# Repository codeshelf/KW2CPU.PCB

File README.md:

KW2CPU.PCB
==========

KW2 radio / CPU PCB design files (with production files). "Brain"

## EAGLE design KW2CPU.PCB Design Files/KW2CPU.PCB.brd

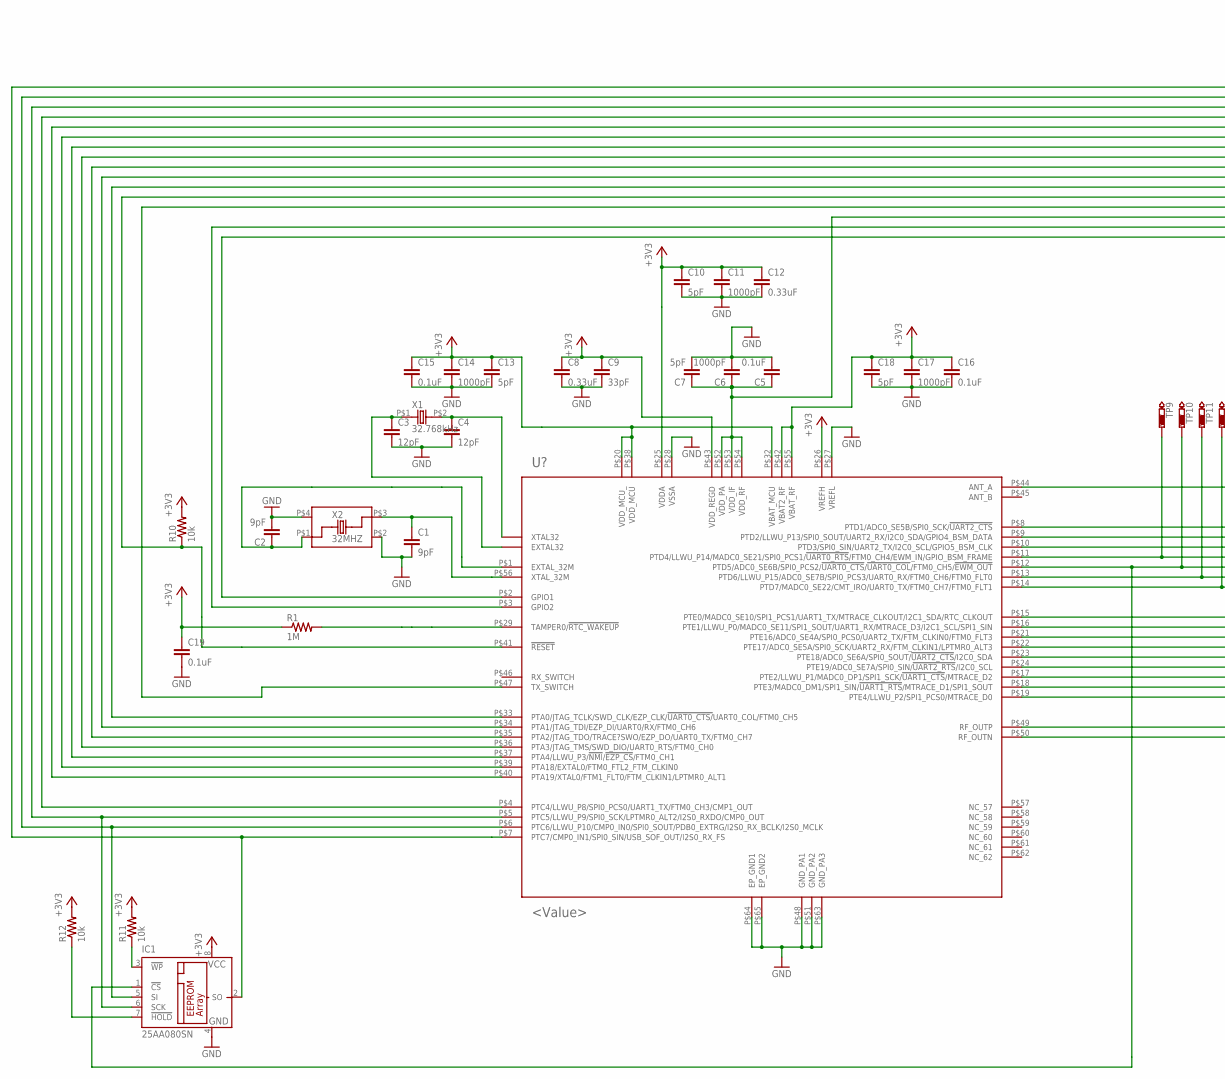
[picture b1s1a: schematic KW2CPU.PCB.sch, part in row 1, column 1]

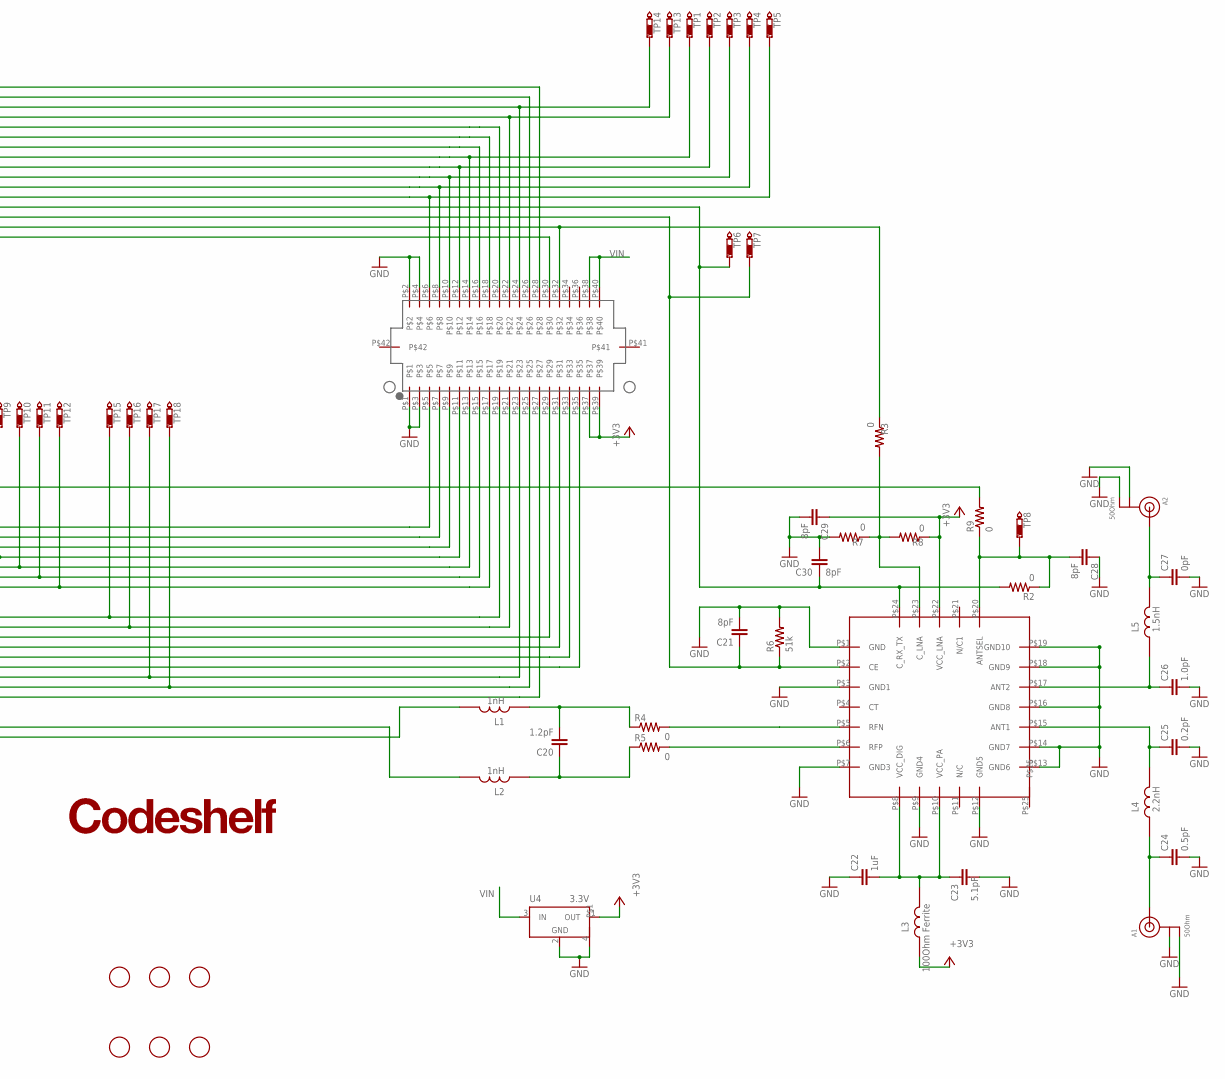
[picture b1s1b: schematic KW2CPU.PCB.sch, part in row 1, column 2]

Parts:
A1, A2: 50Ohm; U.FL
C1, C2: 9pF; C0402
C3, C4: 12pF; C0402
C5, C15, C16, C19: 0.1uF; C0402
C6, C11, C14, C17: 1000pF; C0402
C7, C10, C13, C18: 5pF; C0402
C8, C12: 0.33uF; C0402
C9: 33pF; C0402
C20: 1.2pF; RF-L0201
C21, C28, C29, C30: 8pF; RFMD0402
C22: 1uF; RF-L0201
C23: 5.1pF; RF-L0201
C24: 0.5pF; RFMD0402
C25: 0.2pF; RFMD0402
C26: 1.0pF; RFMD0402
C27: 0pF; RFMD0402
IC1: 25AA080SN; SO-08; MPN 25AA640A
J1: DF12_M
L1, L2: 1nH; RF-L0201
L3: 100Ohm Ferrite; RFMD0402
L4: 2.2nH; RFMD0402
L5: 1.5nH; RFMD0402
R1: 1M; RF-R0402
R2, R3, R7, R8, R9: 0; RFMD0402
R4, R5: 0; RF-L0201
R6: 51k; RFMD0402
R10, R11, R12: 10k; RF-R0402
TP1, TP2, TP3, TP4, TP5, TP6, TP7, TP8, TP9, TP10, TP11, TP12, TP13, TP14, TP15, TP16, TP17, TP18: PTR1TP15R; TP15R
U1: MKW21D; LGA63
U3: RF6555
U4: 3.3V; SOT223
U$1: CODESHELF-LOGOSMALL; CODESHELF-LOGO-SMALL
U$2, U$3, U$4, U$5, U$6, U$7: FIDUCIAL; FIDUCIAL_1MM
X1: 32.768kHz; 32KHZSMD
X2: 32MHZ; 32MHZSMD

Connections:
!HOLD: IC1.7 (!HOLD), R12.1
!RESET: J1.P$6, R10.1, TP5.TP, U1.P$41 (!RESET)
!WP: IC1.3 (!WP), R11.1
+3V3: C8.1, C9.1, C10.1, C11.1, C12.1, C13.1, C14.1, C15.1, C16.1, C17.1, C18.1, C19.1, C29.P$1 (1), IC1.8 (VCC), J1.P$37, J1.P$39, L3.P$2 (2), R1.1, R8.P$1 (1), R10.2, R11.2, R12.2, U1.P$20 (VDD_MCU_), U1.P$25 (VDDA), U1.P$26 (VREFH), U1.P$32 (VBAT_MCU), U1.P$38 (VDD_MCU), U1.P$42 (VBAT2_RF), U1.P$43 (VDD_REGD), U1.P$55 (VBAT_RF), U3.P$22 (VCC_LNA), U4.1 (OUT)
ANT1: C25.P$1 (1), L4.P$1 (1), U3.P$15 (ANT1)
ANT2: C26.P$1 (1), L5.P$2 (2), U3.P$17 (ANT2)
ANTSEL: C28.P$2 (2), R2.P$1 (1), R9.P$1 (1), TP8.TP, U3.P$20 (ANTSEL)
ANT_A: R9.P$2 (2), U1.P$44 (ANT_A)
C_LNA: R3.P$2 (2), R7.P$1 (1), R8.P$2 (2), U3.P$23 (C_LNA)
EXTAL32: C3.1, U1.P$31 (EXTAL32), X1.P$1 (1)
EXTAL_32M: C2.1, U1.P$1 (EXTAL_32M), X2.P$1
GND: A1.1 (GND), A1.2 (GND), A2.1 (GND), A2.2 (GND), C1.2, C2.2, C3.2, C4.2, C5.2, C6.2, C7.2, C8.2, C9.2, C10.2, C11.2, C12.2, C13.2, C14.2, C15.2, C16.2, C17.2, C18.2, C19.2, C21.P$2 (2), C22.P$1 (1), C23.P$2 (2), C24.P$2 (2), C25.P$2 (2), C26.P$2 (2), C27.P$2 (2), C28.P$1 (1), C29.P$2 (2), C30.P$1 (1), IC1.4 (GND), J1.P$1, J1.P$2, J1.P$3, J1.P$4, R6.P$2 (2), R7.P$2 (2), U1.P$27 (VREFL), U1.P$28 (VSSA), U1.P$48 (GND_PA1), U1.P$51 (GND_PA2), U1.P$63 (GND_PA3), U1.P$64 (EP_GND1), U1.P$65 (EP_GND2), U3.P$1 (GND), U3.P$3 (GND1), U3.P$7 (GND3), U3.P$9 (GND4), U3.P$12 (GND5), U3.P$13 (GND6), U3.P$14 (GND7), U3.P$16 (GND8), U3.P$18 (GND9), U3.P$19 (GND10), U4.2 (GND), U4.4, X2.P$2, X2.P$4
GPIO1: J1.P$30, U1.P$2 (GPIO1)
GPIO2: J1.P$32, R3.P$1 (1), U1.P$3 (GPIO2)
PTA0/JTAG_TCLK/SWD_CLK/EZP_CLK/!UART0_CTS/!UART0_COL/FTM0_CH5: J1.P$8, TP4.TP, U1.P$33 (PTA0/JTAG_TCLK/SWD_CLK/EZP_CLK/!UART0_C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)
PTA1/JTAG_TDI/EZP_DI/UART0/RX/FTM0_CH6: J1.P$10, TP3.TP, U1.P$34 (PTA1/JTAG_TDI/EZP_DI/UART0/RX/FTM0_CH6)
PTA2/JTAG_TDO/TRACE?SWO/EZP_DO/UART0_TX/FTM0_CH7: J1.P$12, TP2.TP, U1.P$35 (PTA2/JTAG_TDO/TRACE?SWO/EZP_DO/UART0_TX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)
PTA3/JTAG_TMS/SWD_DIO/UART0_RTS/FTM0_CH0: J1.P$14, TP1.TP, U1.P$36 (PTA3/JTAG_TMS/SWD_DIO/UART0_RTS/FTM0_CH0)
PTA4/LLWU_P3/!NMI!/!EZP_CS!/FTM0_CH1: J1.P$16, U1.P$37 (PTA4/LLWU_P3/!NMI!/!EZP_CS!/FTM0_CH1)
PTA18/EXTAL0/FTM0_FTL2_FTM_CLKIN0: J1.P$18, U1.P$39 (PTA18/EXTAL0/FTM0_FTL2_FTM_CLKIN0)
PTA19/XTAL0/FTM1_FLT0/FTM_CLKIN1/LPTMR0_ALT1: J1.P$20, U1.P$40 (PTA19/XTAL0/FTM1_FLT0/FTM_CLKIN1/LPTMR0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)
PTC4/LLWU_P8/SPI0_PCS0/UART1_TX/FTM0_CH3/CMP1_OUT: J1.P$22, TP13.TP, U1.P$4 (PTC4/LLWU_P8/SPI0_PCS0/UART1_TX/FTM0_CH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)
PTC5/LLWU_P9/SPI0_SCK/LPTMR0_ALT2/I2S0_RXDO/CMP0_OUT: IC1.6 (SCK), J1.P$24, TP14.TP, U1.P$5 (PTC5/LLWU_P9/SPI0_SCK/LPTMR0_ALT2/I2S0_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)
PTC6/LLWU_P10/CMP0_IN0/SPI0_SOUT/PDB0_EXTRG/I2S0_RX_BCLK/I2S0_MCLK: IC1.5 (SI), J1.P$26, U1.P$6 (PTC6/LLWU_P10/CMP0_IN0/SPI0_SOUT/PDB0_E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)
PTC7/CMP0_IN1/SPI0_SIN/USB_SOF_OUT/I2S0_RX_FS: IC1.2 (SO), J1.P$28, U1.P$7 (PTC7/CMP0_IN1/SPI0_SIN/USB_SOF_OUT/I2S0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)
PTD1/ADC0_SE5B/SPI0_SCK/!UART2_CTS: J1.P$5, U1.P$8 (PTD1/ADC0_SE5B/SPI0_SCK/!UART2_CTS)
PTD2/LLWU_P13/SPI0_SOUT/UART2_RX/I2C0_SDA/GPIO4_BSM_DATA: J1.P$7, U1.P$9 (PTD2/LLWU_P13/SPI0_SOUT/UART2_RX/I2C0_S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)
PTD3/SPI0_SIN/UART2_TX/I2C0_SCL/GPIO5_BSM_CLK: J1.P$9, U1.P$10 (PTD3/SPI0_SIN/UART2_TX/I2C0_SCL/GPIO5_B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)
PTD4/LLWU_P14/MADC0_SE21/SPI0_PCS1/!UART0_RTS!/FTM0_CH4/EWM_IN/GPIO_BSM_FRAME: J1.P$11, TP9.TP, U1.P$11 (PTD4/LLWU_P14/MADC0_SE21/SPI0_PCS1/!UAR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)
PTD5/ADC0_SE6B/SPI0_PCS2/!UART0_CTS!/!UART0_COL!/FTM0_CH5/!EWM_OUT: IC1.1 (!CS), J1.P$13, TP10.TP, U1.P$12 (PTD5/ADC0_SE6B/SPI0_PCS2/!UART0_CTS!/!U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)
PTD6/LLWU_P15/ADC0_SE7B/SPI0_PCS3/UART0_RX/FTM0_CH6/FTM0_FLT0: J1.P$15, TP11.TP, U1.P$13 (PTD6/LLWU_P15/ADC0_SE7B/SPI0_PCS3/UART0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)
PTD7/MADC0_SE22/CMT_IRO/UART0_TX/FTM0_CH7/FTM0_FLT1: J1.P$17, TP12.TP, U1.P$14 (PTD7/MADC0_SE22/CMT_IRO/UART0_TX/FTM0_C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)
PTE0/MADC0_SE10/SPI1_PCS1/UART1_TX/MTRACE_CLKOUT/I2C1_SDA/RTC_CLKOUT: J1.P$19, TP15.TP, U1.P$15 (PTE0/MADC0_SE10/SPI1_PCS1/UART1_TX/MTRA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)
PTE1/LLWU_P0/MADC0_SE11/SPI1_SOUT/UART1_RX/MTRACE_D3/I2C1_SCL/SPI1_SIN: J1.P$21, TP16.TP, U1.P$16 (PTE1/LLWU_P0/MADC0_SE11/SPI1_SOUT/UART1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)
PTE2/LLWU_P1/MADC0_DP1/SPI1_SCK/!UART1_CTS!/MTRACE_D2: J1.P$23, TP17.TP, U1.P$17 (PTE2/LLWU_P1/MADC0_DP1/SPI1_SCK/!UART1_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)
PTE3/MADC0_DM1/SPI1_SIN/!UART1_RTS!/MTRACE_D1/SPI1_SOUT: J1.P$25, TP18.TP, U1.P$18 (PTE3/MADC0_DM1/SPI1_SIN/!UART1_RTS!/MTR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)
PTE4/LLWU_P2/SPI1_PCS0/MTRACE_D0: J1.P$27, U1.P$19 (PTE4/LLWU_P2/SPI1_PCS0/MTRACE_D0)
PTE16/ADC0_SE4A/SPI0_PCS0/UART2_TX/FTM_CLKIN0/FTM0_FLT3: J1.P$29, U1.P$21 (PTE16/ADC0_SE4A/SPI0_PCS0/UART2_TX/FTM_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)
PTE17/ADC0_SE5A/SPI0_SCK/UART2_RX/FTM_CLKIN1/LPTMR0_ALT3: J1.P$31, U1.P$22 (PTE17/ADC0_SE5A/SPI0_SCK/UART2_RX/FTM_C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)
PTE18/ADC0_SE6A/SPI0_SOUT/!UART2_CTS!/I2C0_SDA: J1.P$33, U1.P$23 (PTE18/ADC0_SE6A/SPI0_SOUT/!UART2_CTS!/I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)
PTE19/ADC0_SE7A/SPI0_SIN/!UART2_RTS!/I2C0_SCL: J1.P$35, U1.P$24 (PTE19/ADC0_SE7A/SPI0_SIN/!UART2_RTS!/I2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)
RADIO_AREG: C5.1, C6.1, C7.1, C21.P$1 (1), R6.P$1 (1), TP7.TP, U1.P$52 (VDD_PA), U1.P$53 (VDD_IF), U1.P$54 (VDD_RF), U3.P$2 (CE)
RFN: R4.P$2 (2), U3.P$5 (RFN)
RFN_MATCH: C20.P$2 (2), L1.P$2 (2), R4.P$1 (1)
RFP: R5.P$2 (2), U3.P$6 (RFP)
RFP_MATCH: C20.P$1 (1), L2.P$2 (2), R5.P$1 (1)
RF_OUTN: L1.P$1 (1), U1.P$50 (RF_OUTN)
RF_OUTP: L2.P$1 (1), U1.P$49 (RF_OUTP)
TAMPER/!RTC_WAKEUP: R1.2, U1.P$29 (TAMPER0/!RTC_WAKEUP)
TX_SWITCH: C30.P$2 (2), R2.P$2 (2), TP6.TP, U1.P$47 (TX_SWITCH), U3.P$24 (C_RX_TX)
U.FL.ANT1: A1.3 (SIGNAL), C24.P$1 (1), L4.P$2 (2)
U.FL.ANT2: A2.3 (SIGNAL), C27.P$1 (1), L5.P$1 (1)
VCC_DIG_PA: C22.P$2 (2), C23.P$1 (1), L3.P$1 (1), U3.P$8 (VCC_DIG), U3.P$10 (VCC_PA)
VIN: J1.P$38, J1.P$40, U4.3 (IN)
XTAL32: C4.1, U1.P$30 (XTAL32), X1.P$2 (2)
XTAL_32M: C1.1, U1.P$56 (XTAL_32M), X2.P$3

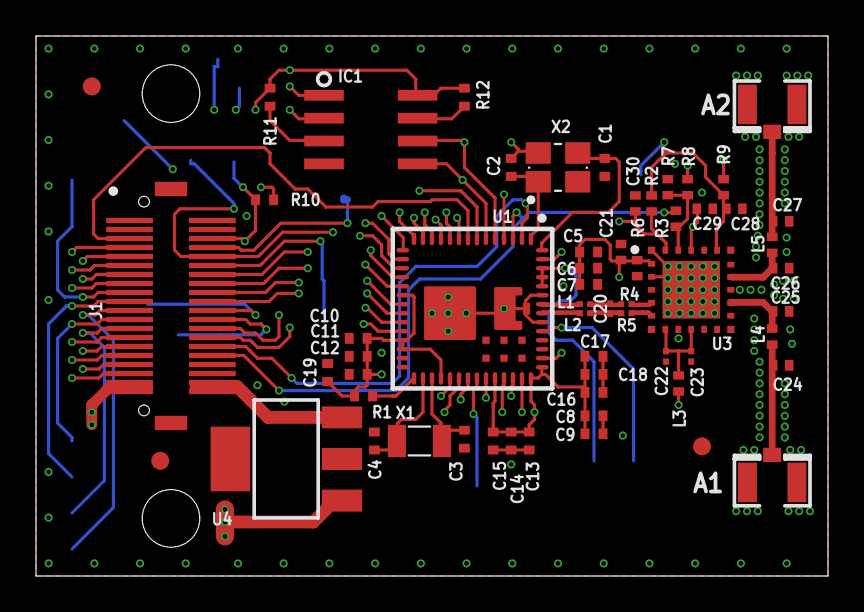
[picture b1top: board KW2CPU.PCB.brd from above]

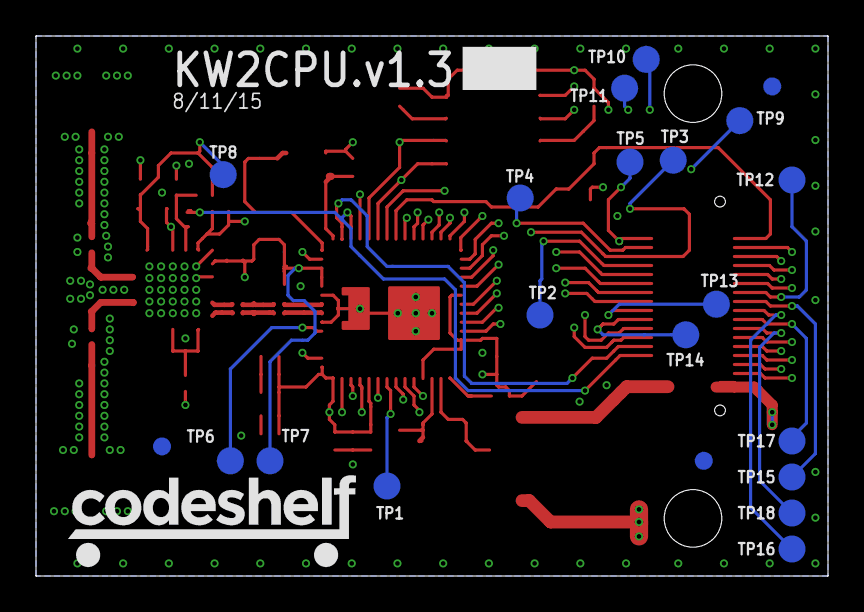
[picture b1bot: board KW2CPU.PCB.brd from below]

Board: 4 copper layers, 44.0 x 30.0 mm, 81 parts (22 on the bottom side), 56 nets.

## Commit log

2014-10-12 Imported KW2CPU design files
    Imported from Archive repo and deleted that one
2014-10-13 Working on layout
    ...4 layers is kind of annoying.
2014-10-13 Still routing
    :(
2014-10-18 Added JTAG
    Topside connector. Still needs routing
2014-10-21 JTAG, RF Conn trace
    Added JTAG connector, adjusted arcs on RF connector trace and added GND
    vias
2014-10-22 Random things
    Mostly playing with copper settings. No design changes
2014-10-31 Rotated board
2014-11-05 Schematic fix
    Almost done fixing schematic
2014-11-07 Added hacky JTAG board
    Terrible angles, but fininshed. Can be made in house (0.2mm)
2014-11-12 Labeled all nets
    Named nets and simplified JTAG adapter board.
2014-11-13 Fixed RefDes, issues with names disappearing
    Names on layout disappearing (for RF front end parts)
2014-11-14 Added test points
    JTAG and front-end control test points
2014-11-19 Added timing TPs
    For radio calibration. Also exported CAD model
2014-11-19 Fixed PTC5 label and added RESET pullup
2014-11-20 Switched Flash for EEPROM
2014-11-22 Added part numbers and manufacturers (inconsistent)
    Also moved files to proper directories. Needs manual inconsistency
    fixing
2014-11-22 Exporting production files in progress
    Creating production files. Missing: ECO, Stackup, Drill
2014-11-22 KW2CPU.PCB.v.1.0 First Article Release
    Added drill file, ECO and FAB notes.
2014-11-22 KW2CPU.PCB.v1.0
    Fixed name decimal point
2014-12-16 Fixed Vreg part #, changed JTAG holes
    Added /DB suffix to VReg and reexported BOM (identify package), fixed
    JTAG holes (try square). No design changes in BRAIN, just layer view
    options.
2014-12-20 KW2CPU.PCB.v1.1 Release
    Fixed Gerbers (omitted layer), fixed BOM suffixes (see ECO), tented vias
    and antenna holes in Eagle (and Gerbers), added Stackup -> Layer in Fab
    notes.
2015-01-16 Fixed PTC5 net name
2015-02-07 KW2CPU.PCB.v1.2 Release
    DNP Voltage regulator (BOM change + schematic attribute, ECO),
    incremented silkscreen to v1.2, fixed name on BOM filr (added .BOM)
2015-05-20 First cut at v1.3 (antenna diversity)
    * Antenna diversity
    * ISO layouts
    * More TPs
    * Axial anchors
    * Remvoe top JTAG connector
2015-06-11 Layout changes
2015-07-01 KW2 v1.3 revisions
    The first big slug of KW2 revisions.
2015-07-01 Fix RF6555
    Align the GND vias
2015-07-24 Fixes after Rafael's review
    * DNP all but the dedicated RX/TX antenna select option via GPIO2.
    * DNP all but the LNA passthrough control option.
2015-07-24 Connect RF6555 CE to KW2 AREG
2015-07-29 Impedance ajustments
    Also removed old production files. Adjusted differential pair and
    single-ended traces.
2015-07-29 Fixed grid units, adjusted vias
    Moved and adjusted all GND vias near RF traces
2015-07-31 Updated traces for impedance
    As per RoyalCircuits recommendation
2015-08-05 Minor adjustments (silkscreen, DNPs)
    Added silkscren RefDes for antenna connectors, RFMD and Hirose
    connector. Added PN for antenna connector, DNP for match neworks and
    re-exported CSV BOM
2015-08-07 KW2CPU.PCB.v1.3P1
    Design and production files for new KW2
2015-08-11 KW2CPU.PCB.v1.3P1 (Revision)
    Added GND strips + vias for RF foam, fixed silkscreen, moved regulator
    to accomodate new hole position (from before) and removed vias under
    KW2. New production files sent to Calla for quoting / prototype run
2015-08-11 Omitted brd file from commit
